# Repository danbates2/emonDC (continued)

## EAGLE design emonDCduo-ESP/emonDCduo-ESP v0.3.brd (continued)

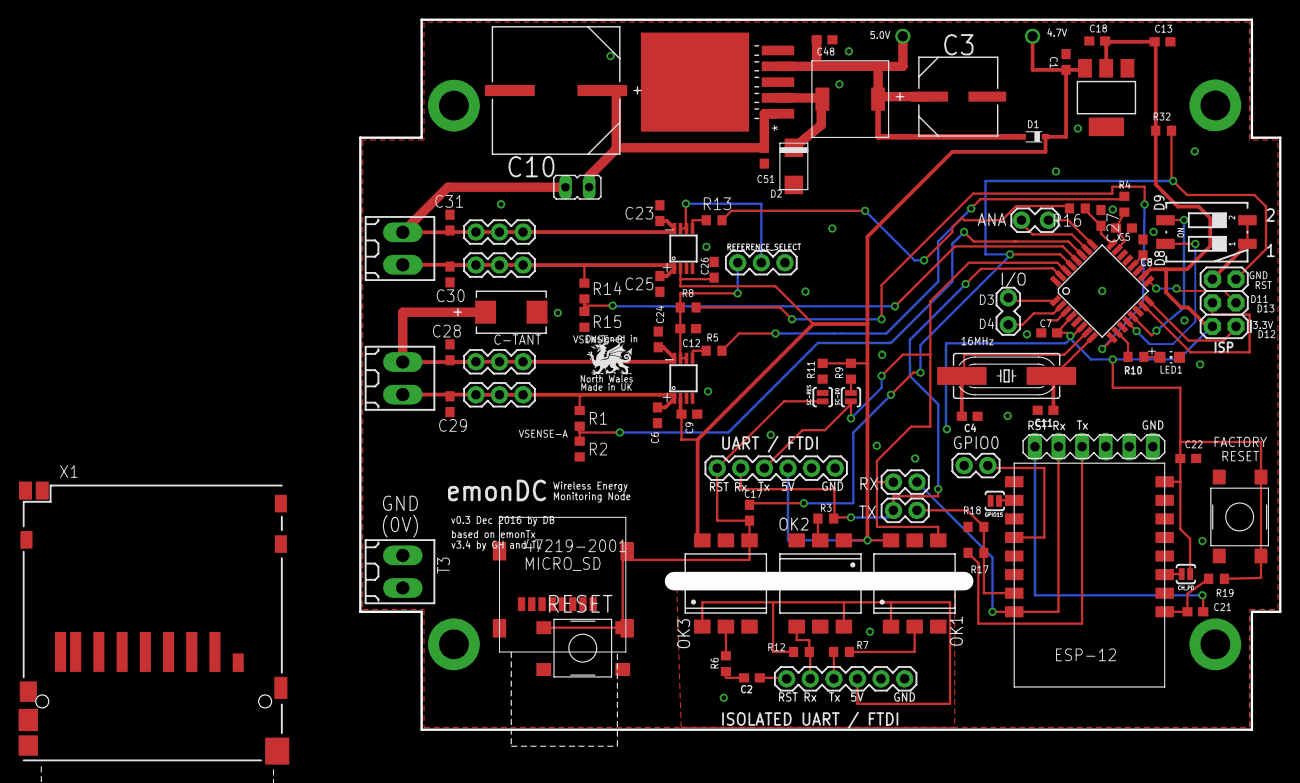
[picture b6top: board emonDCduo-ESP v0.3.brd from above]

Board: 2 copper layers, 99.1 x 76.5 mm, 91 parts (1 on the bottom side), 64 nets.
